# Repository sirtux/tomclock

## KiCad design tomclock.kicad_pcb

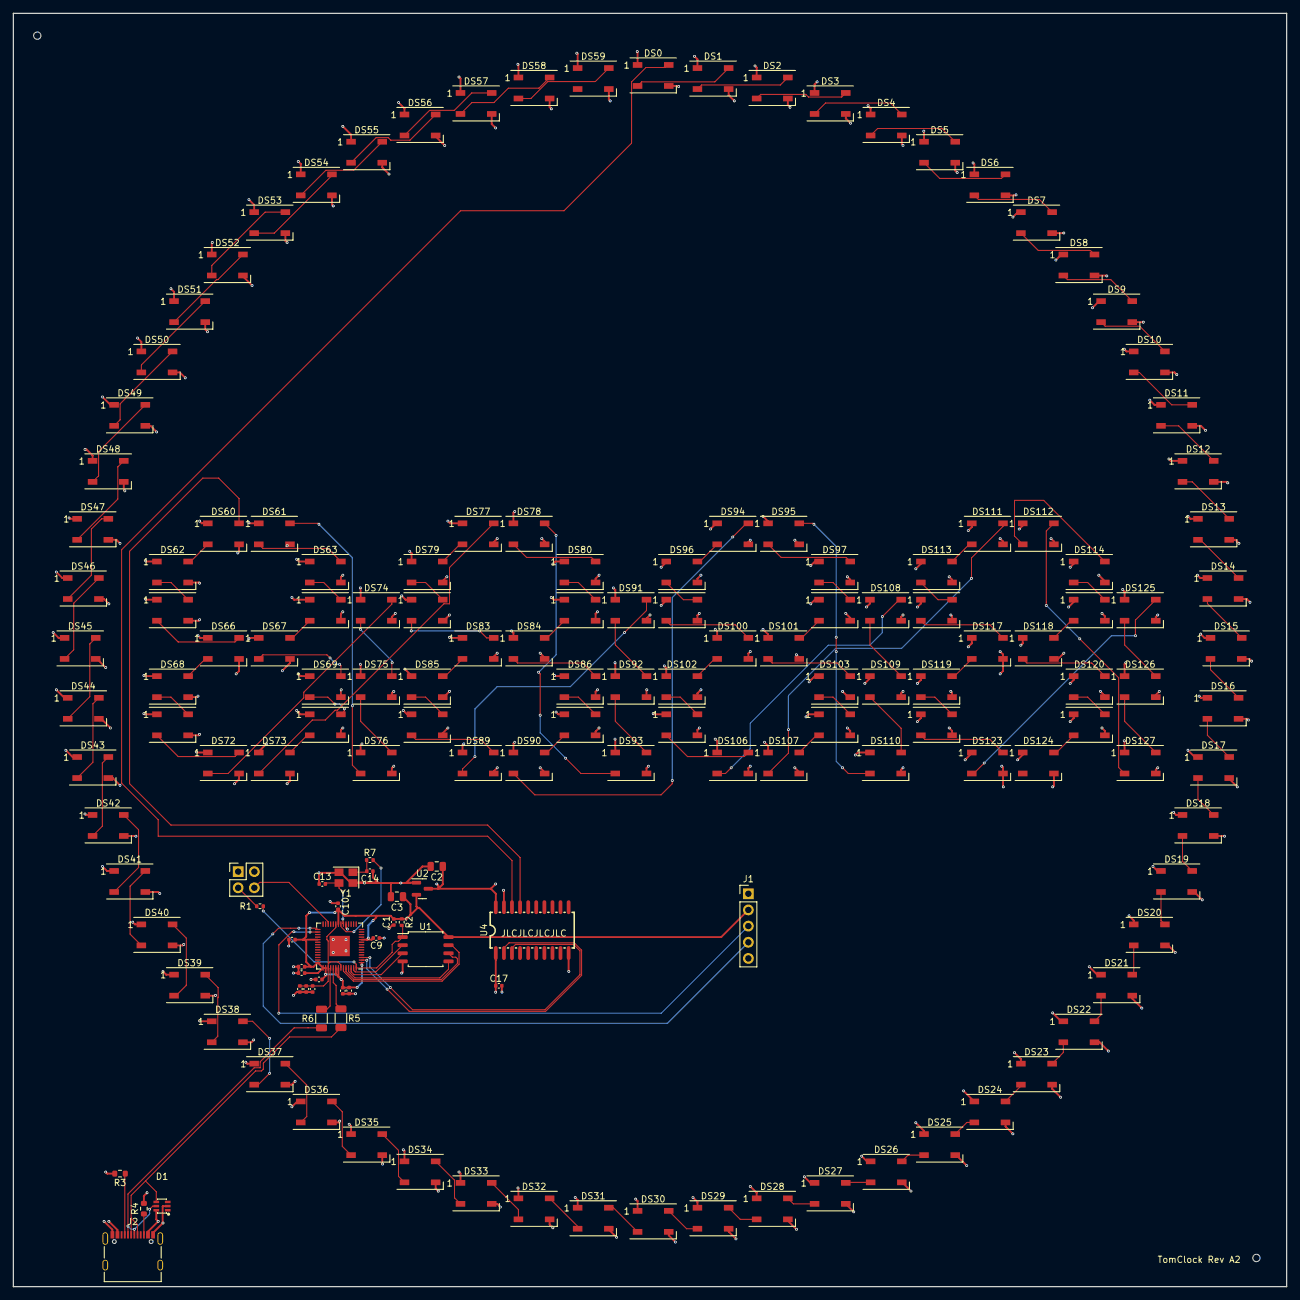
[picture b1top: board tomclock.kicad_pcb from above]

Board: 4 copper layers, 200.0 x 200.0 mm, 163 parts (0 on the bottom side), 153 nets.

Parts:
C1, C4, C5, C7, C9, C10, C11, C12, C15, C16, C17: 100n; C_0402_1005Metric
C2, C3: 10u; C_0805_2012Metric
C6, C8: 1u; C_0402_1005Metric
C13, C14: 27 pF; C_0402_1005Metric
D1: SMF05CT1G; SOT-363_L2.0-W1.3-P0.65-LS2.1-BR
DS0, DS1, DS2, DS3, DS4, DS5, DS6, DS7, DS8, DS9, DS10, DS11, DS12, DS13, DS14, DS15, DS16, DS17, DS18, DS19, DS20, DS21, DS22, DS23, DS24, DS25, DS26, DS27, DS28, DS29, DS30, DS31, DS32, DS33, DS34, DS35, DS36, DS37, DS38, DS39, DS40, DS41, DS42, DS43, DS44, DS45, DS46, DS47, DS48, DS49, DS50, DS51, DS52, DS53, DS54, DS55, DS56, DS57, DS58, DS59, DS60, DS61, DS62, DS63, DS64, DS65, DS66, DS67, DS68, DS69, DS70, DS71, DS72, DS73, DS74, DS75, DS76, DS77, DS78, DS79, DS80, DS81, DS82, DS83, DS84, DS85, DS86, DS87, DS88, DS89, DS90, DS91, DS92, DS93, DS94, DS95, DS96, DS97, DS98, DS99, DS100, DS101, DS102, DS103, DS104, DS105, DS106, DS107, DS108, DS109, DS110, DS111, DS112, DS113, DS114, DS115, DS116, DS117, DS118, DS119, DS120, DS121, DS122, DS123, DS124, DS125, DS126, DS127: WS2812B; LED_WS2812B_PLCC4_5.0x5.0mm_P3.2mm
H1, H2: MountingHole; ToolingHole_JLCSMT
J1: I2C_Conn; PinHeader_1x05_P2.54mm_Vertical
J2: USB_C_Receptacle_USB2.0; USB_C_Receptacle_Palconn_UTC16-G
J5: Boot/Reset; PinHeader_2x02_P2.54mm_Vertical
R1, R7: 1k; R_0402_1005Metric
R2: DNF; R_0402_1005Metric
R3, R4: 5.1k; R_0603_1608Metric
R5: 27.6; R_1206_3216Metric
R6: 27.4; R_1206_3216Metric
U1: W25Q128JVS; SOIC-8_5.23x5.23mm_P1.27mm
U2: XC6206P332MR; SOT-23
U3: RP2040; QFN-56-1EP_7x7mm_P0.4mm_EP3.2x3.2mm
U4: 74HCT245; SOIC-20_L13.3-W5.5-P1.27-LS7.8-BL
Y1: 12MHz; Crystal_SMD_3225-4Pin_3.2x2.5mm

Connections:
+1V1: C4.1, C5.1, C6.1, U3.23 (DVDD), U3.45 (VREG_VOUT), U3.50 (DVDD)
+3V3: C1.2, C3.1, C7.2, C8.1, C9.2, C10.2, C11.2, C12.2, C15.2, C16.2, J1.2, R2.1, U1.8 (VCC), U2.2 (VO), U3.1 (IOVDD), U3.10 (IOVDD), U3.22 (IOVDD), U3.33 (IOVDD), U3.42 (IOVDD), U3.43 (ADC_AVDD), U3.44 (VREG_IN), U3.48 (USB_VDD), U3.49 (IOVDD)
/Digit1/DIGIT_IN: DS60.4 (DIN), U4.17 (B2)
/Digit1/DIGIT_OUT: DS73.2 (DOUT), DS77.4 (DIN)
/Digit1/S9: DS61.4 (DIN), DS76.2 (DOUT)
/Digit2/DIGIT_OUT: DS90.2 (DOUT), DS94.4 (DIN)
/Digit2/S9: DS78.4 (DIN), DS93.2 (DOUT)
/Digit3/DIGIT_OUT: DS107.2 (DOUT), DS111.4 (DIN)
/Digit3/S9: DS95.4 (DIN), DS110.2 (DOUT)
/Digit4/S9: DS112.4 (DIN), DS127.2 (DOUT)
/GPIO19_I2C1_SCL: J1.4, U3.29 (GPIO18)
/GPIO19_I2C1_SDA: J1.3, U3.30 (GPIO19)
/LEDCircle/S9: DS9.2 (DOUT), DS10.4 (DIN)
/LEDCircle/S19: DS19.2 (DOUT), DS20.4 (DIN)
/LEDCircle/S29: DS29.2 (DOUT), DS30.4 (DIN)
/LEDCircle/S39: DS39.2 (DOUT), DS40.4 (DIN)
/LEDCircle/S49: DS49.2 (DOUT), DS50.4 (DIN)
/LEDCircle/SECOND_IN: DS0.4 (DIN), U4.18 (B1)
/rp2040_base/GPIO0: U3.2 (GPIO0), U4.2 (A1)
/rp2040_base/GPIO1: U3.3 (GPIO1), U4.3 (A2)
/rp2040_base/QSPI_SCLK: U1.6 (CLK), U3.52 (QSPI_SCLK)
/rp2040_base/QSPI_SD0: U1.5 (DI(IO0)), U3.53 (QSPI_SD0)
/rp2040_base/QSPI_SD1: U1.2 (DO(IO1)), U3.55 (QSPI_SD1)
/rp2040_base/QSPI_SD2: U1.3 (IO2), U3.54 (QSPI_SD2)
/rp2040_base/QSPI_SD3: U1.7 (IO3), U3.51 (QSPI_SD3)
/rp2040_base/QSPI_SS: R1.2, R2.2, U1.1 (~CS), U3.56 (QSPI_SS)
/rp2040_base/RESET: J5.4, U3.26 (RUN)
/rp2040_base/USB_BOOT: J5.3, R1.1
/rp2040_base/USB_C_D+: D1.4, J2.A6 (D+), J2.B6 (D+), R5.1
/rp2040_base/USB_C_D-: D1.5, J2.A7 (D-), J2.B7 (D-), R6.1
/rp2040_base/XIN: C13.2, U3.20 (XIN), Y1.3
/rp2040_base/XOUT: R7.2, U3.21 (XOUT)
GND: C1.1, C2.2, C3.2, C4.2, C5.2, C6.2, C7.1, C8.2, C9.1, C10.1, C11.1, C12.1, C13.1, C14.1, C15.1, C16.1, C17.2, D1.2, DS0.3 (VSS), DS1.3 (VSS), DS2.3 (VSS), DS3.3 (VSS), DS4.3 (VSS), DS5.3 (VSS), DS6.3 (VSS), DS7.3 (VSS), DS8.3 (VSS), DS9.3 (VSS), DS10.3 (VSS), DS11.3 (VSS), DS12.3 (VSS), DS13.3 (VSS), DS14.3 (VSS), DS15.3 (VSS), DS16.3 (VSS), DS17.3 (VSS), DS18.3 (VSS), DS19.3 (VSS), DS20.3 (VSS), DS21.3 (VSS), DS22.3 (VSS), DS23.3 (VSS), DS24.3 (VSS), DS25.3 (VSS), DS26.3 (VSS), DS27.3 (VSS), DS28.3 (VSS), DS29.3 (VSS), DS30.3 (VSS), DS31.3 (VSS), DS32.3 (VSS), DS33.3 (VSS), DS34.3 (VSS), DS35.3 (VSS), DS36.3 (VSS), DS37.3 (VSS), DS38.3 (VSS), DS39.3 (VSS), DS40.3 (VSS), DS41.3 (VSS), DS42.3 (VSS), DS43.3 (VSS), DS44.3 (VSS), DS45.3 (VSS), DS46.3 (VSS), DS47.3 (VSS), DS48.3 (VSS), DS49.3 (VSS), DS50.3 (VSS), DS51.3 (VSS), DS52.3 (VSS), DS53.3 (VSS), DS54.3 (VSS), DS55.3 (VSS), DS56.3 (VSS), DS57.3 (VSS), DS58.3 (VSS), DS59.3 (VSS), DS60.3 (VSS), DS61.3 (VSS), DS62.3 (VSS), DS63.3 (VSS), DS64.3 (VSS), DS65.3 (VSS), DS66.3 (VSS), DS67.3 (VSS), DS68.3 (VSS), DS69.3 (VSS), DS70.3 (VSS), DS71.3 (VSS), DS72.3 (VSS), DS73.3 (VSS), DS74.3 (VSS), DS75.3 (VSS), DS76.3 (VSS), DS77.3 (VSS), DS78.3 (VSS), DS79.3 (VSS), DS80.3 (VSS), DS81.3 (VSS), DS82.3 (VSS), DS83.3 (VSS), DS84.3 (VSS), DS85.3 (VSS), DS86.3 (VSS), DS87.3 (VSS), DS88.3 (VSS), DS89.3 (VSS), DS90.3 (VSS), DS91.3 (VSS), DS92.3 (VSS), DS93.3 (VSS), DS94.3 (VSS), DS95.3 (VSS), DS96.3 (VSS), DS97.3 (VSS), DS98.3 (VSS), DS99.3 (VSS), DS100.3 (VSS), DS101.3 (VSS), DS102.3 (VSS), DS103.3 (VSS), DS104.3 (VSS), DS105.3 (VSS), DS106.3 (VSS), DS107.3 (VSS), DS108.3 (VSS), DS109.3 (VSS), DS110.3 (VSS), DS111.3 (VSS), DS112.3 (VSS), DS113.3 (VSS), DS114.3 (VSS), DS115.3 (VSS), DS116.3 (VSS), DS117.3 (VSS), DS118.3 (VSS), DS119.3 (VSS), DS120.3 (VSS), DS121.3 (VSS), DS122.3 (VSS), DS123.3 (VSS), DS124.3 (VSS), DS125.3 (VSS), DS126.3 (VSS), DS127.3 (VSS), J1.1, J2.A1 (GND), J2.A12 (GND), J2.B1 (GND), J2.B12 (GND), J2.S1 (SHIELD), J5.1, J5.2, R3.2, R4.2, U1.4 (GND), U2.1 (GND), U3.19 (TESTEN), U3.57 (GND), U4.10 (GND), U4.19 (#OE), Y1.2, Y1.4
unnamed: C14.2, R7.1, Y1.1
unnamed: DS0.2 (DOUT), DS1.4 (DIN)
unnamed: DS1.2 (DOUT), DS2.4 (DIN)
unnamed: DS2.2 (DOUT), DS3.4 (DIN)
unnamed: DS3.2 (DOUT), DS4.4 (DIN)
unnamed: DS4.2 (DOUT), DS5.4 (DIN)
unnamed: DS5.2 (DOUT), DS6.4 (DIN)
unnamed: DS6.2 (DOUT), DS7.4 (DIN)
unnamed: DS7.2 (DOUT), DS8.4 (DIN)
unnamed: DS8.2 (DOUT), DS9.4 (DIN)
unnamed: DS10.2 (DOUT), DS11.4 (DIN)
unnamed: DS11.2 (DOUT), DS12.4 (DIN)
unnamed: DS12.2 (DOUT), DS13.4 (DIN)
unnamed: DS13.2 (DOUT), DS14.4 (DIN)
unnamed: DS14.2 (DOUT), DS15.4 (DIN)
unnamed: DS15.2 (DOUT), DS16.4 (DIN)
unnamed: DS16.2 (DOUT), DS17.4 (DIN)
unnamed: DS17.2 (DOUT), DS18.4 (DIN)
unnamed: DS18.2 (DOUT), DS19.4 (DIN)
unnamed: DS20.2 (DOUT), DS21.4 (DIN)
unnamed: DS21.2 (DOUT), DS22.4 (DIN)
unnamed: DS22.2 (DOUT), DS23.4 (DIN)
unnamed: DS23.2 (DOUT), DS24.4 (DIN)
unnamed: DS24.2 (DOUT), DS25.4 (DIN)
unnamed: DS25.2 (DOUT), DS26.4 (DIN)
unnamed: DS26.2 (DOUT), DS27.4 (DIN)
unnamed: DS27.2 (DOUT), DS28.4 (DIN)
unnamed: DS28.2 (DOUT), DS29.4 (DIN)
unnamed: DS30.2 (DOUT), DS31.4 (DIN)
unnamed: DS31.2 (DOUT), DS32.4 (DIN)
unnamed: DS32.2 (DOUT), DS33.4 (DIN)
unnamed: DS33.2 (DOUT), DS34.4 (DIN)
unnamed: DS34.2 (DOUT), DS35.4 (DIN)
unnamed: DS35.2 (DOUT), DS36.4 (DIN)
unnamed: DS36.2 (DOUT), DS37.4 (DIN)
unnamed: DS37.2 (DOUT), DS38.4 (DIN)
unnamed: DS38.2 (DOUT), DS39.4 (DIN)
unnamed: DS40.2 (DOUT), DS41.4 (DIN)
unnamed: DS41.2 (DOUT), DS42.4 (DIN)
unnamed: DS42.2 (DOUT), DS43.4 (DIN)
unnamed: DS43.2 (DOUT), DS44.4 (DIN)
unnamed: DS44.2 (DOUT), DS45.4 (DIN)
unnamed: DS45.2 (DOUT), DS46.4 (DIN)
unnamed: DS46.2 (DOUT), DS47.4 (DIN)
unnamed: DS47.2 (DOUT), DS48.4 (DIN)
unnamed: DS48.2 (DOUT), DS49.4 (DIN)
unnamed: DS50.2 (DOUT), DS51.4 (DIN)
unnamed: DS51.2 (DOUT), DS52.4 (DIN)
unnamed: DS52.2 (DOUT), DS53.4 (DIN)
unnamed: DS53.2 (DOUT), DS54.4 (DIN)
unnamed: DS54.2 (DOUT), DS55.4 (DIN)
unnamed: DS55.2 (DOUT), DS56.4 (DIN)
unnamed: DS56.2 (DOUT), DS57.4 (DIN)
unnamed: DS57.2 (DOUT), DS58.4 (DIN)
unnamed: DS58.2 (DOUT), DS59.4 (DIN)
unnamed: DS60.2 (DOUT), DS62.4 (DIN)
unnamed: DS61.2 (DOUT), DS63.4 (DIN)
unnamed: DS62.2 (DOUT), DS64.4 (DIN)
unnamed: DS63.2 (DOUT), DS65.4 (DIN)
unnamed: DS64.2 (DOUT), DS66.4 (DIN)
unnamed: DS65.2 (DOUT), DS67.4 (DIN)
unnamed: DS66.2 (DOUT), DS68.4 (DIN)
unnamed: DS67.2 (DOUT), DS69.4 (DIN)
unnamed: DS68.2 (DOUT), DS70.4 (DIN)
unnamed: DS69.2 (DOUT), DS71.4 (DIN)
unnamed: DS70.2 (DOUT), DS72.4 (DIN)
unnamed: DS71.2 (DOUT), DS73.4 (DIN)
unnamed: DS72.2 (DOUT), DS74.4 (DIN)
unnamed: DS74.2 (DOUT), DS75.4 (DIN)
unnamed: DS75.2 (DOUT), DS76.4 (DIN)
unnamed: DS77.2 (DOUT), DS79.4 (DIN)
unnamed: DS78.2 (DOUT), DS80.4 (DIN)
unnamed: DS79.2 (DOUT), DS81.4 (DIN)
unnamed: DS80.2 (DOUT), DS82.4 (DIN)
unnamed: DS81.2 (DOUT), DS83.4 (DIN)
unnamed: DS82.2 (DOUT), DS84.4 (DIN)
unnamed: DS83.2 (DOUT), DS85.4 (DIN)
unnamed: DS84.2 (DOUT), DS86.4 (DIN)
unnamed: DS85.2 (DOUT), DS87.4 (DIN)
unnamed: DS86.2 (DOUT), DS88.4 (DIN)
unnamed: DS87.2 (DOUT), DS89.4 (DIN)
unnamed: DS88.2 (DOUT), DS90.4 (DIN)
unnamed: DS89.2 (DOUT), DS91.4 (DIN)
unnamed: DS91.2 (DOUT), DS92.4 (DIN)
unnamed: DS92.2 (DOUT), DS93.4 (DIN)
unnamed: DS94.2 (DOUT), DS96.4 (DIN)
unnamed: DS95.2 (DOUT), DS97.4 (DIN)
unnamed: DS96.2 (DOUT), DS98.4 (DIN)
unnamed: DS97.2 (DOUT), DS99.4 (DIN)
unnamed: DS98.2 (DOUT), DS100.4 (DIN)
unnamed: DS100.2 (DOUT), DS102.4 (DIN)
unnamed: DS99.2 (DOUT), DS101.4 (DIN)
unnamed: DS101.2 (DOUT), DS103.4 (DIN)
unnamed: DS102.2 (DOUT), DS104.4 (DIN)
unnamed: DS103.2 (DOUT), DS105.4 (DIN)
unnamed: DS104.2 (DOUT), DS106.4 (DIN)
unnamed: DS105.2 (DOUT), DS107.4 (DIN)
unnamed: DS106.2 (DOUT), DS108.4 (DIN)
unnamed: DS108.2 (DOUT), DS109.4 (DIN)
unnamed: DS109.2 (DOUT), DS110.4 (DIN)
unnamed: DS111.2 (DOUT), DS113.4 (DIN)
unnamed: DS112.2 (DOUT), DS114.4 (DIN)
unnamed: DS113.2 (DOUT), DS115.4 (DIN)
unnamed: DS114.2 (DOUT), DS116.4 (DIN)
unnamed: DS115.2 (DOUT), DS117.4 (DIN)
unnamed: DS116.2 (DOUT), DS118.4 (DIN)
unnamed: DS117.2 (DOUT), DS119.4 (DIN)
unnamed: DS118.2 (DOUT), DS120.4 (DIN)
unnamed: DS119.2 (DOUT), DS121.4 (DIN)
unnamed: DS120.2 (DOUT), DS122.4 (DIN)
unnamed: DS121.2 (DOUT), DS123.4 (DIN)
unnamed: DS122.2 (DOUT), DS124.4 (DIN)
unnamed: DS123.2 (DOUT), DS125.4 (DIN)
unnamed: DS125.2 (DOUT), DS126.4 (DIN)
unnamed: DS126.2 (DOUT), DS127.4 (DIN)
unnamed: J2.A5 (CC1), R3.1
unnamed: J2.B5 (CC2), R4.1
unnamed: R6.2, U3.46 (USB_DM)
unnamed: R5.2, U3.47 (USB_DP)
VBUS: C2.1, C17.1, D1.6, DS0.1 (VDD), DS1.1 (VDD), DS2.1 (VDD), DS3.1 (VDD), DS4.1 (VDD), DS5.1 (VDD), DS6.1 (VDD), DS7.1 (VDD), DS8.1 (VDD), DS9.1 (VDD), DS10.1 (VDD), DS11.1 (VDD), DS12.1 (VDD), DS13.1 (VDD), DS14.1 (VDD), DS15.1 (VDD), DS16.1 (VDD), DS17.1 (VDD), DS18.1 (VDD), DS19.1 (VDD), DS20.1 (VDD), DS21.1 (VDD), DS22.1 (VDD), DS23.1 (VDD), DS24.1 (VDD), DS25.1 (VDD), DS26.1 (VDD), DS27.1 (VDD), DS28.1 (VDD), DS29.1 (VDD), DS30.1 (VDD), DS31.1 (VDD), DS32.1 (VDD), DS33.1 (VDD), DS34.1 (VDD), DS35.1 (VDD), DS36.1 (VDD), DS37.1 (VDD), DS38.1 (VDD), DS39.1 (VDD), DS40.1 (VDD), DS41.1 (VDD), DS42.1 (VDD), DS43.1 (VDD), DS44.1 (VDD), DS45.1 (VDD), DS46.1 (VDD), DS47.1 (VDD), DS48.1 (VDD), DS49.1 (VDD), DS50.1 (VDD), DS51.1 (VDD), DS52.1 (VDD), DS53.1 (VDD), DS54.1 (VDD), DS55.1 (VDD), DS56.1 (VDD), DS57.1 (VDD), DS58.1 (VDD), DS59.1 (VDD), DS60.1 (VDD), DS61.1 (VDD), DS62.1 (VDD), DS63.1 (VDD), DS64.1 (VDD), DS65.1 (VDD), DS66.1 (VDD), DS67.1 (VDD), DS68.1 (VDD), DS69.1 (VDD), DS70.1 (VDD), DS71.1 (VDD), DS72.1 (VDD), DS73.1 (VDD), DS74.1 (VDD), DS75.1 (VDD), DS76.1 (VDD), DS77.1 (VDD), DS78.1 (VDD), DS79.1 (VDD), DS80.1 (VDD), DS81.1 (VDD), DS82.1 (VDD), DS83.1 (VDD), DS84.1 (VDD), DS85.1 (VDD), DS86.1 (VDD), DS87.1 (VDD), DS88.1 (VDD), DS89.1 (VDD), DS90.1 (VDD), DS91.1 (VDD), DS92.1 (VDD), DS93.1 (VDD), DS94.1 (VDD), DS95.1 (VDD), DS96.1 (VDD), DS97.1 (VDD), DS98.1 (VDD), DS99.1 (VDD), DS100.1 (VDD), DS101.1 (VDD), DS102.1 (VDD), DS103.1 (VDD), DS104.1 (VDD), DS105.1 (VDD), DS106.1 (VDD), DS107.1 (VDD), DS108.1 (VDD), DS109.1 (VDD), DS110.1 (VDD), DS111.1 (VDD), DS112.1 (VDD), DS113.1 (VDD), DS114.1 (VDD), DS115.1 (VDD), DS116.1 (VDD), DS117.1 (VDD), DS118.1 (VDD), DS119.1 (VDD), DS120.1 (VDD), DS121.1 (VDD), DS122.1 (VDD), DS123.1 (VDD), DS124.1 (VDD), DS125.1 (VDD), DS126.1 (VDD), DS127.1 (VDD), J2.A4 (VBUS), J2.A9 (VBUS), J2.B4 (VBUS), J2.B9 (VBUS), U2.3 (VI), U4.1 (DIR), U4.20 (VCC)

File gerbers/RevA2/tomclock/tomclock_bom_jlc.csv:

"Comment","Designator","Footprint","LCSC Part #"
"10u","C2,C3","C_0805_2012Metric","C15850"
"1u","C6,C8","C_0402_1005Metric","C52923"
"27 pF","C13,C14","C_0402_1005Metric","C1557"
"100n","C17,C1,C4,C5,C7,C9,C10,C11,C12,C15,C16","C_0402_1005Metric","C1525"
"WS2812B","DS0,DS1,DS2,DS3,DS4,DS5,DS6,DS7,DS8,DS9,DS10,DS11,DS12,DS13,DS14,DS15,DS16,DS17,DS18,DS19,DS20,DS21,DS22,DS23,DS24,DS25,DS26,DS27,DS28,DS29,DS30,DS31,DS32,DS33,DS34,DS35,DS36,DS37,DS38,DS39,DS40,DS41,DS42,DS43,DS44,DS45,DS46,DS47,DS48,DS49,DS50,DS52,DS53,DS54,DS55,DS56,DS57,DS58,DS59,DS60,DS61,DS62,DS63,DS64,DS65,DS66,DS67,DS68,DS69,DS70,DS71,DS72,DS73,DS74,DS75,DS76,DS77,DS78,DS79,DS80,DS81,DS82,DS83,DS84,DS85,DS86,DS87,DS88,DS89,DS90,DS91,DS92,DS93,DS94,DS95,DS96,DS97,DS98,DS99,DS100,DS101,DS102,DS103,DS104,DS105,DS106,DS107,DS108,DS109,DS110,DS111,DS112,DS113,DS114,DS115,DS116,DS117,DS118,DS119,DS120,DS121,DS122,DS123,DS124,DS125,DS126,DS127","LED_WS2812B_PLCC4_5.0x5.0mm_P3.2mm","C2761795"
"S2812B","DS51","LED_WS2812B_PLCC4_5.0x5.0mm_P3.2mm","C2761795"
"USB_C_Receptacle_USB2.0","J2","USB_C_Receptacle_Palconn_UTC16-G","C167321"
"1k","R1,R7","R_0402_1005Metric","C11702"
"5.1k","R3,R4","R_0603_1608Metric","C23186"
"27.4","R5,R6","R_0201_0603Metric","C423620"
"W25Q128JVS","U1","SOIC-8_5.23x5.23mm_P1.27mm","C97521"
"XC6206P332MR","U2","SOT-23","C5446"
"RP2040","U3","QFN-56-1EP_7x7mm_P0.4mm_EP3.2x3.2mm","C2040"
"74HCT245","U4","SOIC-20W_7.5x12.8mm_P1.27mm","C5979"
"12MHz","Y1","Crystal_SMD_3225-4Pin_3.2x2.5mm","C9002"

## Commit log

2023-04-30 Added .gitignore
2023-04-30 Initial Release
2023-04-30 Schematic: Update symbols, add esd protection, add I2C header
2023-04-30 PCB: Updated new components, removed old paths
2023-04-30 PCB: SilkScreen Updates
2023-05-01 JLC: Fixup for JLC Production
2023-05-01 MicroPython Code to run the thing
2023-05-15 Change to timer interrupt
2023-05-18 Added software
2025-05-04 Implemented useful timezone magic
2025-05-04 Enhance .gitignore
2025-05-04 Bump kicad version
